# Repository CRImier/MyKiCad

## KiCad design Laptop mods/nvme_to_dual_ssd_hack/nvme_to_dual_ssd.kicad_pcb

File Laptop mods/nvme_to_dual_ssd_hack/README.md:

# M.2 NVMe to dual SSD adapter - with M.2 hack

This is an adapter board to put two SSDs in a M.2 slot that only accepts one,
it achieves that by abusing the PCI-E and M.2 specifications and relying on the
system firmware to be a bit deficient.

This adapter can only work in slots that accept either a PCI-E SSD or a SATA SSD.
It switches the slot into the SATA mode, but relies on PCI-E REFCLK and lanes 2&3
to be present. It uses lanes 2&3 as PCI-E lanes for the PCI-E SSD, connecting
lane 3 to SSD's lane 0 and lane 2 to SSD lane 1. This kind of lane reversal is
in the PCI-E spec, but it's not clear whether it's implemented in chipsets available out there,
and which chipsets it could be compatible with.

There's two ways to implement PCI-E/SATA muxing for an M.2 drive. First way relies on a
a Pericom-made (or similar) mux that switches either PCI-E or SATA to your M.2 slot,
depending on the CONFIG1 pin state. This means that both PCI-E and SATA are present
at the external mux, whereas REFCLK and PCI-E lanes 1-3 are hardwired to the slot.

Second way is where muxing is done inside the chipset itself, using hybrid lanes that
can be either PCI-E or SATA, depending on chipset's internal configuration. So, the CONFIG1
signal goes to the chipset, and the SSD is connected to the chipset directly, with all four lanes.
It's not clear if lanes 1-3 and REFCLK are disabled when a SATA SSD is inserted - if so,
this adapter will not work unless you somehow find a way for this not to happen.
Which is to say, if this adapter is used on a laptop with an internal mux, it relies on the
PCI-E lanes 1-3 and REFCLK to stay enabled.

At this point, I wish I had some kind of way to produce 100MHz REFCLK with an overall
small footprint. I really don't know... after all, REFCLK is often produced by a different
chip on the motherboard, or a different part of the chipset. Any ideas? Anyone?

You can only tell which kind of mux is being used by looking over the motherboard. If it has
a mux near the SSD socket, then it's an external mux kind of deal. If there's no mux
in sight, then the mux is inside the chipset. In fact, I have two Asus motherboards
that come from similar laptops, both equipped with a Ryzen 3500U (chipset on the same package
as CPU), yet one of them uses an external mux and one of them uses the internal one.
Of course, my daily driver laptop just had to be the one with the internal mux!

This adapter should be plug&play, *provided* that your hardware can be subverted in this kind of way.

This board has no decoupling capacitors, and you're on your own when it comes to managing 3.3V power draw
of two SSDs in a slot designed to power one. There seems to be enough 3.3V pins in an M-key slot for two SSDs,
conceptually (each M.2 pin is 0.5A max, 9x0.5A = 4.5A), but I give you no guarantees that it works out for you power-wise.

If your chipset disables the PCI-E when it detects a SATA SSD, I can't help you with that, I'm sorry.
Sometimes, if you have an external mux for that signal, the detection line also goes to the chipset -
then, you can track it down and break the connection.

There are resistors on the bottom for interrupting PCI-E&other control signals
if any of them interfere with operation of your SSD:

* 1 interrupts DAA/DSS
* 2 interrupts DEVSLP
* 3 interrupts PERST (PCI-E only)
* 4 interrupts CLKREQ (PCI-E only)
* 5 interrupts PEWAKE (PCI-E only)
* 6 interrupts SUSCLK

This board is untested and there's no guarantees of fitness.

- PCB size: 22x80mm
- Layer count: 2
- Recommended thickness: 0.8mm (it's an M.2 card, it has to be 0.8mm)

If you need this specific board, contact me - I don't sell it yet because it's untested. A less cursed (and actually tested) variation of this board is available on Tindie!

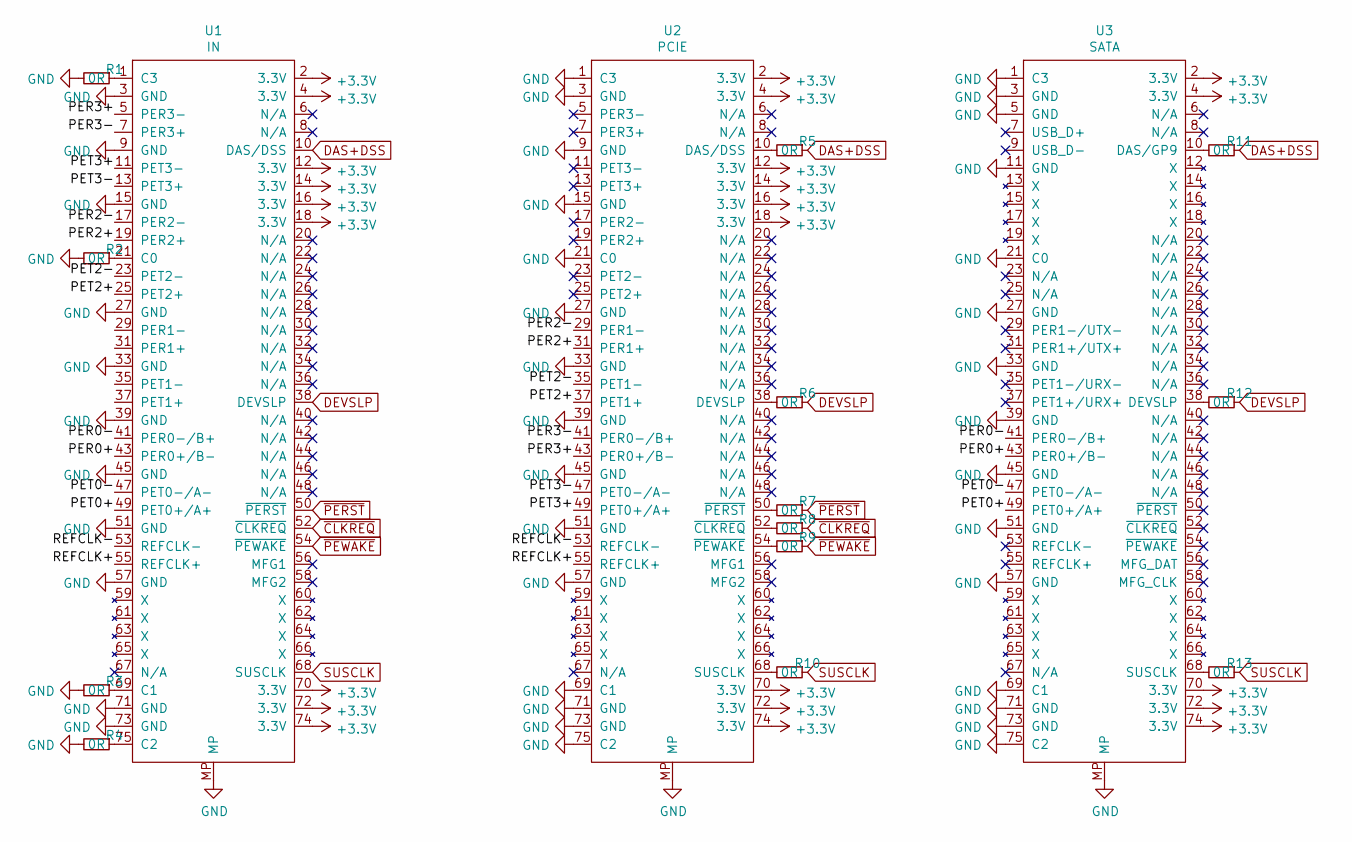
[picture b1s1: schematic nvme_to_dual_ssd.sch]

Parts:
R1, R2, R3, R4, R5, R6, R7, R8, R9, R10, R11, R12, R13: 0R; R_0402_1005Metric
U1: IN; NGFF_M
U2: PCIE; Conn_TE-M.2-0.5-67P-doublesided_TypeM
U3: SATA; Conn_TE-M.2-0.5-67P-doublesided_TypeB

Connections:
+3V3: U1.2 (3.3V), U1.4 (3.3V), U1.12 (3.3V), U1.14 (3.3V), U1.16 (3.3V), U1.18 (3.3V), U1.70 (3.3V), U1.72 (3.3V), U1.74 (3.3V), U2.2 (3.3V), U2.4 (3.3V), U2.12 (3.3V), U2.14 (3.3V), U2.16 (3.3V), U2.18 (3.3V), U2.70 (3.3V), U2.72 (3.3V), U2.74 (3.3V), U3.2 (3.3V), U3.4 (3.3V), U3.70 (3.3V), U3.72 (3.3V), U3.74 (3.3V)
/PER0+: U1.43 (PER0+/B-), U3.43 (PER0+/B-)
/PER0-: U1.41 (PER0-/B+), U3.41 (PER0-/B+)
/PER2+: U1.19 (PER2+), U2.31 (PER1+)
/PER2-: U1.17 (PER2-), U2.29 (PER1-)
/PER3+: U1.5 (PER3-), U2.43 (PER0+/B-)
/PER3-: U1.7 (PER3+), U2.41 (PER0-/B+)
/PET0+: U1.49 (PET0+/A+), U3.49 (PET0+/A+)
/PET0-: U1.47 (PET0-/A-), U3.47 (PET0-/A-)
/PET2+: U1.25 (PET2+), U2.37 (PET1+)
/PET2-: U1.23 (PET2-), U2.35 (PET1-)
/PET3+: U1.11 (PET3-), U2.49 (PET0+/A+)
/PET3-: U1.13 (PET3+), U2.47 (PET0-/A-)
/REFCLK+: U1.55 (REFCLK+), U2.55 (REFCLK+)
/REFCLK-: U1.53 (REFCLK-), U2.53 (REFCLK-)
DAS+DSS: R5.1, R11.1, U1.10 (DAS/DSS)
DEVSLP: R6.1, R12.1, U1.38 (DEVSLP)
GND: R1.2, R2.2, R3.2, R4.2, U1.3 (GND), U1.9 (GND), U1.15 (GND), U1.27 (GND), U1.33 (GND), U1.39 (GND), U1.45 (GND), U1.51 (GND), U1.57 (GND), U1.71 (GND), U1.73 (GND), U1.MP, U2.1 (C3), U2.3 (GND), U2.9 (GND), U2.15 (GND), U2.21 (C0), U2.27 (GND), U2.33 (GND), U2.39 (GND), U2.45 (GND), U2.51 (GND), U2.57 (GND), U2.69 (C1), U2.71 (GND), U2.73 (GND), U2.75 (C2), U2.MP, U3.1 (C3), U3.3 (GND), U3.5 (GND), U3.11 (GND), U3.21 (C0), U3.27 (GND), U3.33 (GND), U3.39 (GND), U3.45 (GND), U3.51 (GND), U3.57 (GND), U3.69 (C1), U3.71 (GND), U3.73 (GND), U3.75 (C2), U3.MP
unnamed: R1.1, U1.1 (C3)
unnamed: R2.1, U1.21 (C0)
unnamed: R3.1, U1.69 (C1)
unnamed: R4.1, U1.75 (C2)
unnamed: R5.2, U2.10 (DAS/DSS)
unnamed: R6.2, U2.38 (DEVSLP)
unnamed: R7.2, U2.50 (~PERST)
unnamed: R8.2, U2.52 (~CLKREQ)
unnamed: R9.2, U2.54 (~PEWAKE)
unnamed: R10.2, U2.68 (SUSCLK)
unnamed: R11.2, U3.10 (DAS/GP9)
unnamed: R12.2, U3.38 (DEVSLP)
unnamed: R13.2, U3.68 (SUSCLK)
SUSCLK: R10.1, R13.1, U1.68 (SUSCLK)
~CLKREQ: R8.1, U1.52 (~CLKREQ)
~PERST: R7.1, U1.50 (~PERST)
~PEWAKE: R9.1, U1.54 (~PEWAKE)

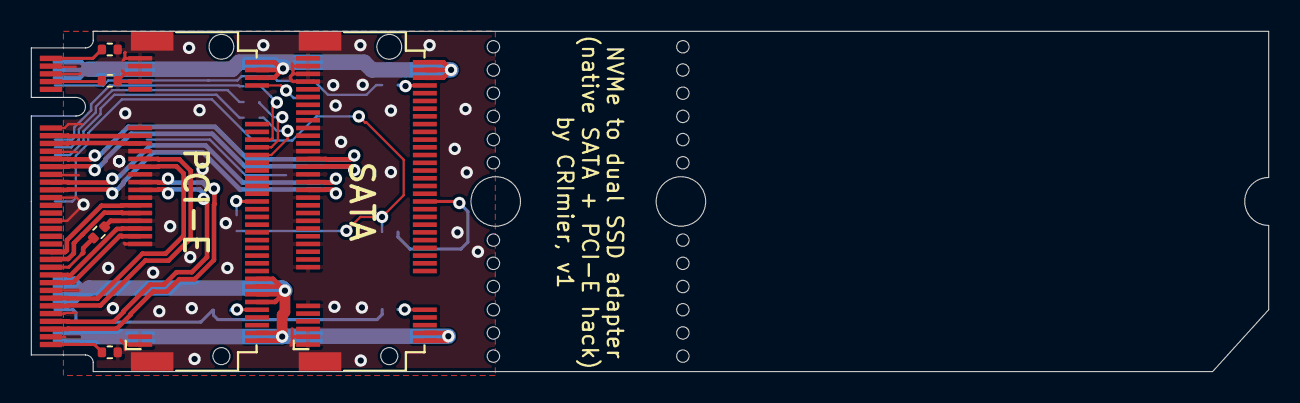
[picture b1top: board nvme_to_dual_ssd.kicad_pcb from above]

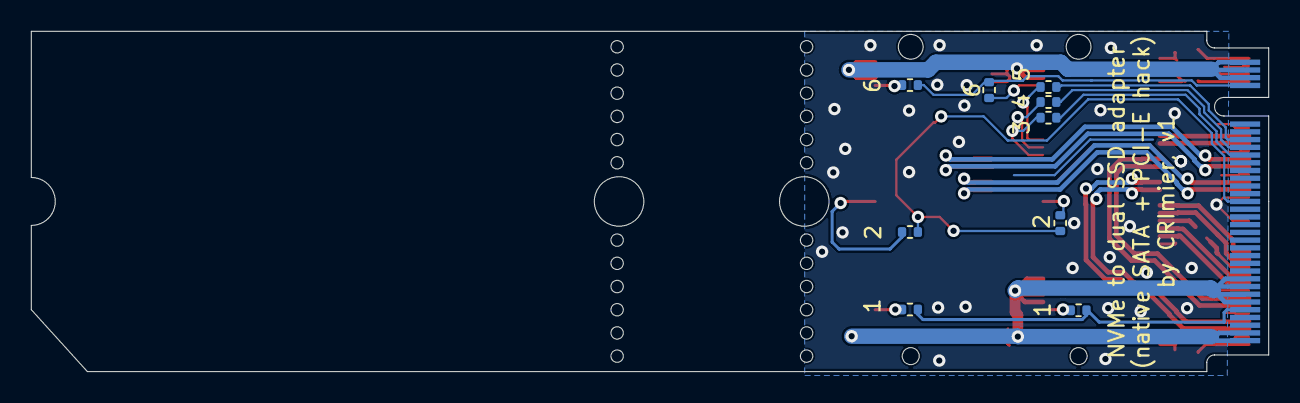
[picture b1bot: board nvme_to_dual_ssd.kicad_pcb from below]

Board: 2 copper layers, 80.0 x 22.0 mm, 16 parts (9 on the bottom side), 35 nets.

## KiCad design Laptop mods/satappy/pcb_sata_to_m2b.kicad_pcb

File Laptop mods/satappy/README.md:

# SATAppy

This is a board that plugs straight into a SATA socket - either one that supports a regular HDD, or one that supports
a laptop sized optical disk drive. It also has a M.2 SATA SSD socket (M-key, but hey).

This board allows you to wire up a SATA cable for any purpose. You can also tap, reconnect or the full-sized SATA power connector power rails.

The SATA routing is daring - this is a 2-layer board, with stubs. There's no redrivers of any kind, either. Impedance has been kinda decreased towards
the 100 ohm target, but not fully.

Currently, the board's outline is not great. I might fix it at some point. If you'd like to manufacture the design or work off it,
contact me, I can find one of these boards I got made and make adjustments to the outline. 

## Notes

- Signal names are silkscreened on the board, top and bottom layers.
- This board is untested and there's no guarantees of fitness.
- I recommend a stencil for assembling this board.

## Info

- Software: Kicad 7
- Version: 1
- PCB size: 25*46mm
- Layer count: 2
- Recommended thickness: 1.2mm (to fit into SATA sockets)

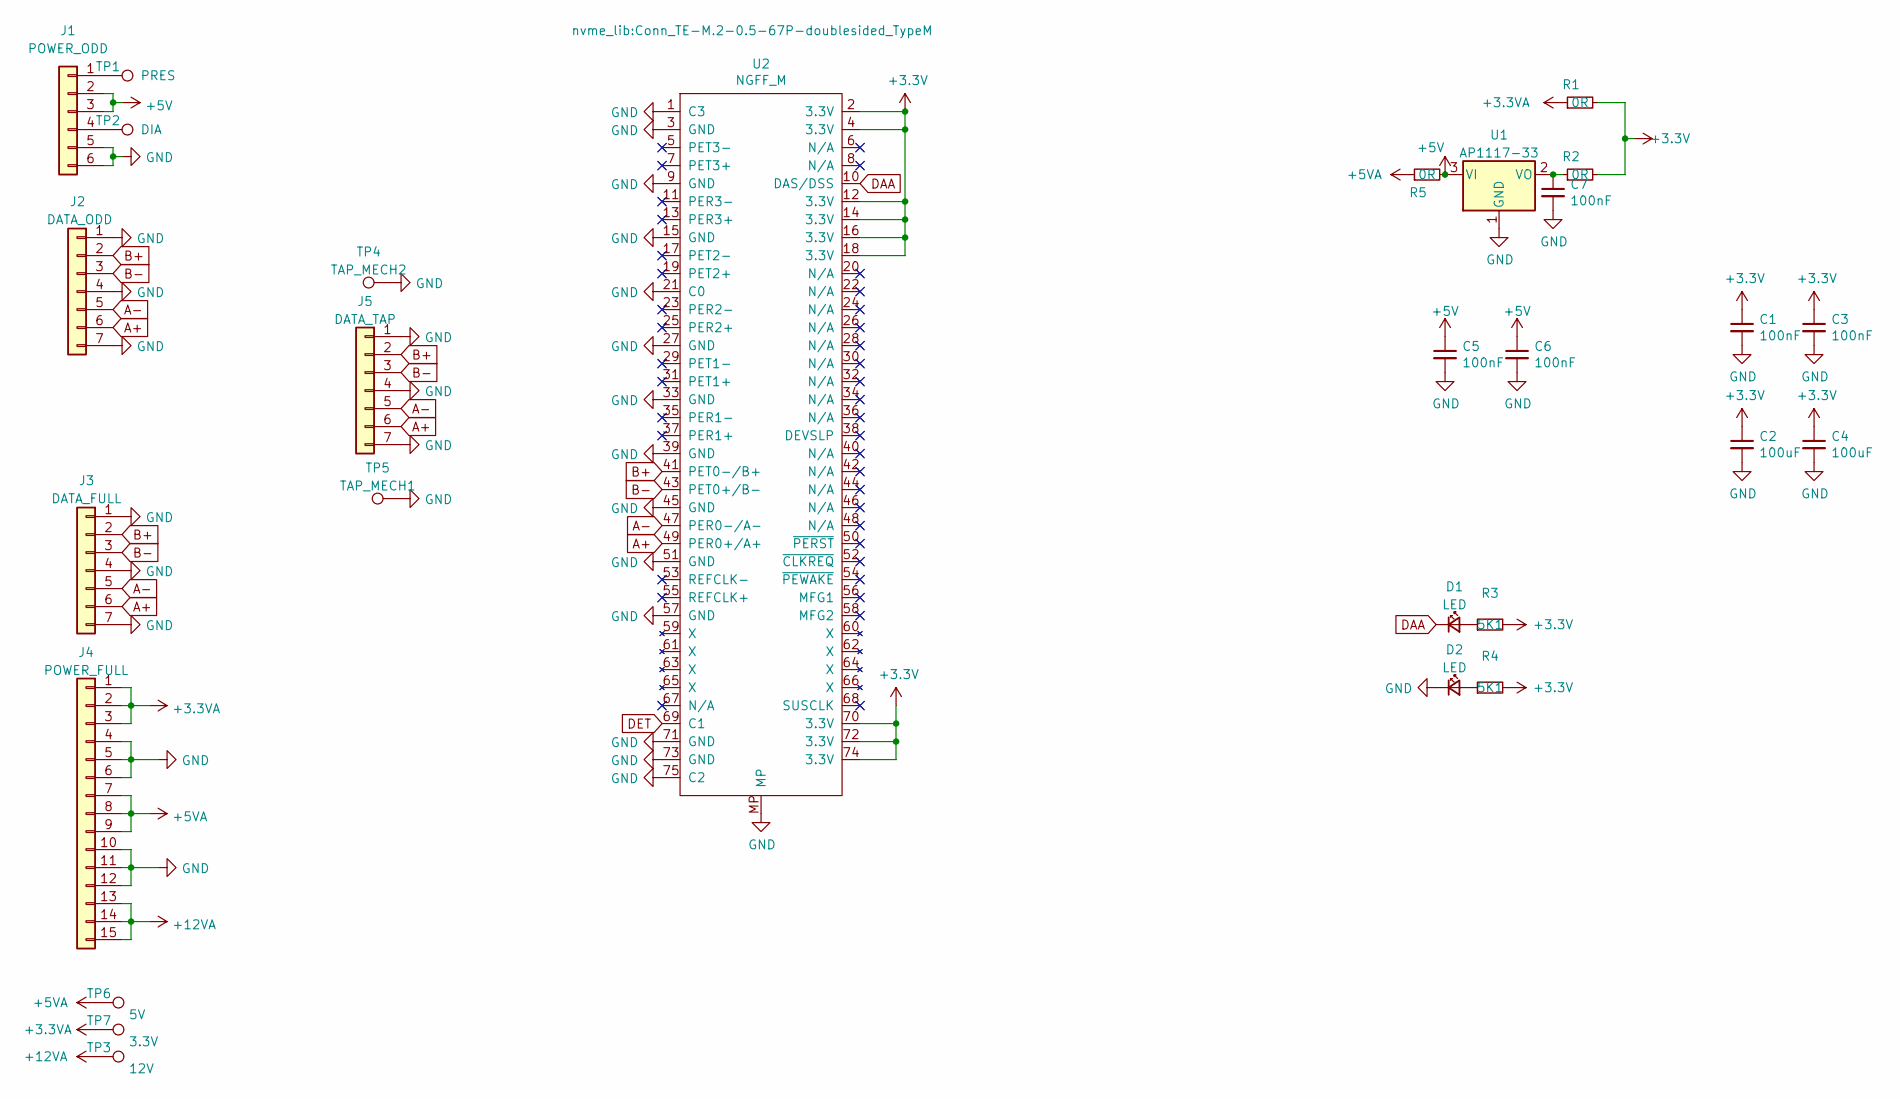
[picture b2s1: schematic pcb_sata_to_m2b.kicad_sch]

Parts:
C1, C3, C6: 100nF; C_0805_2012Metric
C2, C4: 100uF; CP_EIA-2012-12_Kemet-R_Pad1.30x1.05mm_HandSolder
C5, C7: 100nF; CP_EIA-3528-21_Kemet-B_Pad1.50x2.35mm_HandSolder
D1, D2: LED; D_0805_2012Metric
J1: POWER_ODD; SATA_POWER_ODD
J2: DATA_ODD; SATA_SMD
J3: DATA_FULL; SATA_SMD
J4: POWER_FULL; SATA_POWER_FULL
J5: DATA_TAP; PinSocket_1x07_P1.27mm_Vertical
R1, R2, R5: 0R; R_0805_2012Metric
R3, R4: 5K1; R_0603_1608Metric
TP1: PRES; TestPoint_THTPad_D1.5mm_Drill0.7mm
TP2: DIA; TestPoint_THTPad_D1.5mm_Drill0.7mm
TP3: 12V; TestPoint_THTPad_D1.5mm_Drill0.7mm
TP4: TAP_MECH2; TestPoint_Plated_Hole_D2.0mm
TP5: TAP_MECH1; TestPoint_Plated_Hole_D2.0mm
TP6: 5V; TestPoint_THTPad_D1.5mm_Drill0.7mm
TP7: 3.3V; TestPoint_THTPad_D1.5mm_Drill0.7mm
U1: AP1117-33; SOT-223-3_TabPin2
U2: NGFF_M; Conn_TE-M.2-0.5-67P-doublesided_TypeM

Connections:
+3.3VA: J4.1, J4.2, J4.3, R1.1, TP7.1
+3V3: C1.1, C2.1, C3.1, C4.1, R1.2, R2.2, R3.2, R4.2, U2.2 (3.3V), U2.4 (3.3V), U2.12 (3.3V), U2.14 (3.3V), U2.16 (3.3V), U2.18 (3.3V), U2.70 (3.3V), U2.72 (3.3V), U2.74 (3.3V)
+5V: C5.1, C6.1, J1.2, J1.3, R5.2, U1.3 (VI)
+5VA: J4.7, J4.8, J4.9, R5.1, TP6.1
+12VA: J4.13, J4.14, J4.15, TP3.1
A+: J2.6, J3.6, J5.6, U2.49 (PER0+/A+)
A-: J2.5, J3.5, J5.5, U2.47 (PER0-/A-)
B+: J2.2, J3.2, J5.2, U2.41 (PET0-/B+)
B-: J2.3, J3.3, J5.3, U2.43 (PET0+/B-)
DAA: D1.1 (K), U2.10 (DAS/DSS)
DET: U2.69 (C1)
GND: C1.2, C2.2, C3.2, C4.2, C5.2, C6.2, C7.2, D2.1 (K), J1.5, J1.6, J2.1, J2.4, J2.7, J3.1, J3.4, J3.7, J4.4, J4.5, J4.6, J4.10, J4.11, J4.12, J5.1, J5.4, J5.7, TP4.1, TP5.1, U1.1 (GND), U2.1 (C3), U2.3 (GND), U2.9 (GND), U2.15 (GND), U2.21 (C0), U2.27 (GND), U2.33 (GND), U2.39 (GND), U2.45 (GND), U2.51 (GND), U2.57 (GND), U2.71 (GND), U2.73 (GND), U2.75 (C2), U2.MP
unnamed: D1.2 (A), R3.1
unnamed: D2.2 (A), R4.1
unnamed: J1.1, TP1.1
unnamed: J1.4, TP2.1
unnamed: C7.1, R2.1, U1.2 (VO)

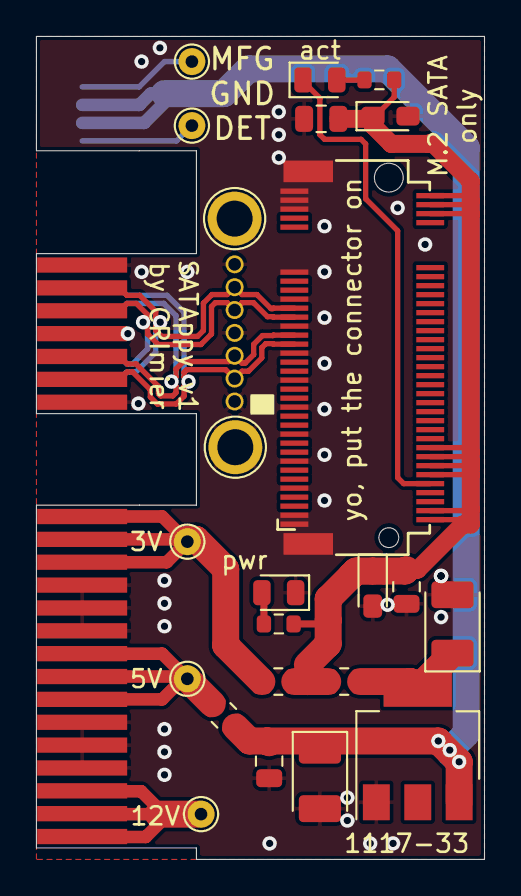
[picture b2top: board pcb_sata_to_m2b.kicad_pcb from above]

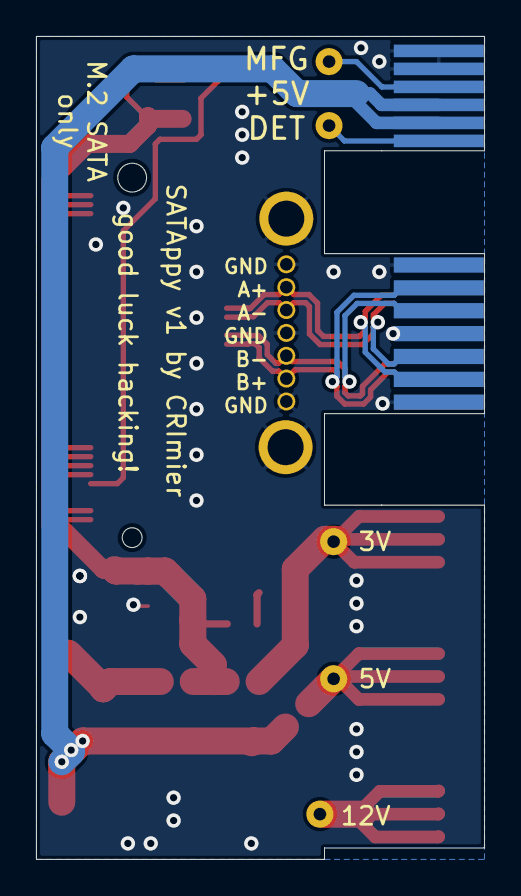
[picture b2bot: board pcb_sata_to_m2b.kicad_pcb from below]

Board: 2 copper layers, 24.9 x 45.7 mm, 28 parts (2 on the bottom side), 16 nets.

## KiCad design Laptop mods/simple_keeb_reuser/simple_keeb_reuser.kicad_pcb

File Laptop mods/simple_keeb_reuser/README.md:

# Simple Keeb Reuser 

This is basically an SPI GPIO expander with 32 bits, designed at laptop keyboard reuse.
PCF8574-like, it has low-strength default pullups and strong pulldowns you can enable.
It's chip shortage-proof, sorta - it's a combination of 595 and 165 chips.
It has two SPI ports, one input-only and one output-only - they're joined into a single port by default.

It's designed for reusing laptop keyboards on the cheap. 
I've designed this during chip shortage times, and never made use of it.
I recommend you use ready-to-go I2C or SPI expander ICs like a normal person.
This is more of a decent test for pick&place machines, at this point.

Has connectors for 1mm, 0.5mm and 0.8mm pitch FPCs, up to 32 pins.

## Notes

- Signal names are silkscreened on the board's bottom layer.
- This repository also includes files for manufacturing a 2x2 panel.
- This board is untested and there's no guarantees of fitness.
- I recommend a stencil for assembling this board - purely for saving yourself some grief, and because of the FPCs, too.

## Info

- Software: Kicad 6
- Version: 1
- PCB size: 49*44mm
- Layer count: 2

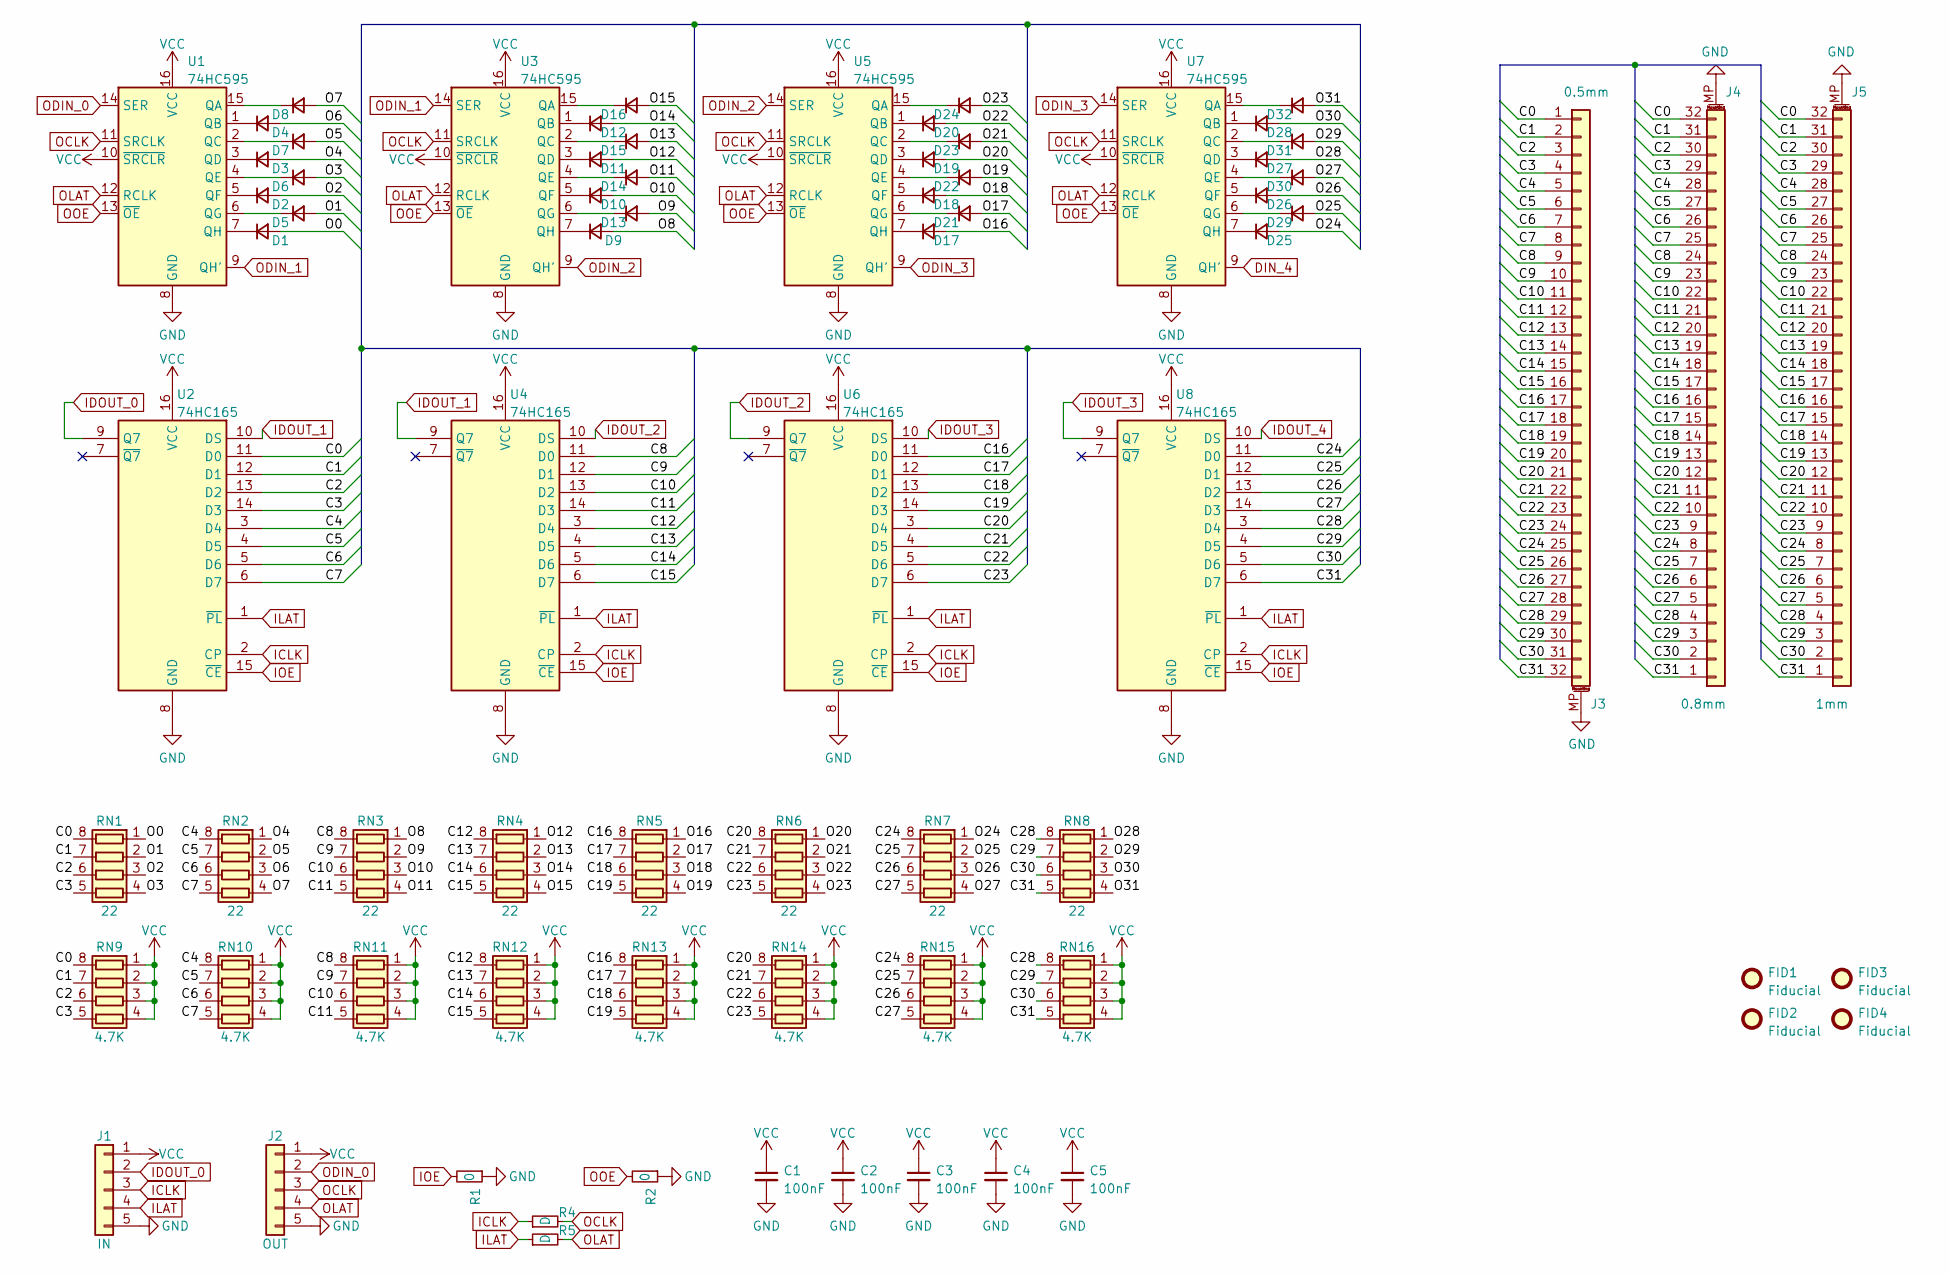
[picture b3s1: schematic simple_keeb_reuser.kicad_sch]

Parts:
C1, C2, C3, C4, C5: 100nF; C_0805_2012Metric
D1, D2, D3, D4, D5, D6, D7, D8, D9, D10, D11, D12, D13, D14, D15, D16, D17, D18, D19, D20, D21, D22, D23, D24, D25, D26, D27, D28, D29, D30, D31, D32: D; D_SOD-123F
FID1, FID2, FID3, FID4: Fiducial; Fiducial_0.75mm_Mask1.5mm
J1: IN; PinHeader_1x05_P2.54mm_Vertical
J2: OUT; PinHeader_1x05_P2.54mm_Vertical
J3: 0.5mm; FPC_40_0.5mm
J4: 0.8mm; FPC_40_0.8mm
J5: 1mm; FPC_40_1mm
R1, R2: 0; R_0603_1608Metric
R4, R5: D; R_0603_1608Metric
RN1, RN2, RN3, RN4, RN5, RN6, RN7, RN8: 22; R_Array_Convex_4x0603
RN9, RN10, RN11, RN12, RN13, RN14, RN15, RN16: 4.7K; R_Array_Convex_4x0603
U1, U3, U5, U7: 74HC595; SO-16_3.9x9.9mm_P1.27mm
U2, U4, U6, U8: 74HC165; SO-16_3.9x9.9mm_P1.27mm

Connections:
/C0: J3.1, J4.32, J5.32, RN1.8 (R1.2), RN9.8 (R1.2), U2.11 (D0)
/C1: J3.2, J4.31, J5.31, RN1.7 (R2.2), RN9.7 (R2.2), U2.12 (D1)
/C2: J3.3, J4.30, J5.30, RN1.6 (R3.2), RN9.6 (R3.2), U2.13 (D2)
/C3: J3.4, J4.29, J5.29, RN1.5 (R4.2), RN9.5 (R4.2), U2.14 (D3)
/C4: J3.5, J4.28, J5.28, RN2.8 (R1.2), RN10.8 (R1.2), U2.3 (D4)
/C5: J3.6, J4.27, J5.27, RN2.7 (R2.2), RN10.7 (R2.2), U2.4 (D5)
/C6: J3.7, J4.26, J5.26, RN2.6 (R3.2), RN10.6 (R3.2), U2.5 (D6)
/C7: J3.8, J4.25, J5.25, RN2.5 (R4.2), RN10.5 (R4.2), U2.6 (D7)
/C8: J3.9, J4.24, J5.24, RN3.8 (R1.2), RN11.8 (R1.2), U4.11 (D0)
/C9: J3.10, J4.23, J5.23, RN3.7 (R2.2), RN11.7 (R2.2), U4.12 (D1)
/C10: J3.11, J4.22, J5.22, RN3.6 (R3.2), RN11.6 (R3.2), U4.13 (D2)
/C11: J3.12, J4.21, J5.21, RN3.5 (R4.2), RN11.5 (R4.2), U4.14 (D3)
/C12: J3.13, J4.20, J5.20, RN4.8 (R1.2), RN12.8 (R1.2), U4.3 (D4)
/C13: J3.14, J4.19, J5.19, RN4.7 (R2.2), RN12.7 (R2.2), U4.4 (D5)
/C14: J3.15, J4.18, J5.18, RN4.6 (R3.2), RN12.6 (R3.2), U4.5 (D6)
/C15: J3.16, J4.17, J5.17, RN4.5 (R4.2), RN12.5 (R4.2), U4.6 (D7)
/C16: J3.17, J4.16, J5.16, RN5.8 (R1.2), RN13.8 (R1.2), U6.11 (D0)
/C17: J3.18, J4.15, J5.15, RN5.7 (R2.2), RN13.7 (R2.2), U6.12 (D1)
/C18: J3.19, J4.14, J5.14, RN5.6 (R3.2), RN13.6 (R3.2), U6.13 (D2)
/C19: J3.20, J4.13, J5.13, RN5.5 (R4.2), RN13.5 (R4.2), U6.14 (D3)
/C20: J3.21, J4.12, J5.12, RN6.8 (R1.2), RN14.8 (R1.2), U6.3 (D4)
/C21: J3.22, J4.11, J5.11, RN6.7 (R2.2), RN14.7 (R2.2), U6.4 (D5)
/C22: J3.23, J4.10, J5.10, RN6.6 (R3.2), RN14.6 (R3.2), U6.5 (D6)
/C23: J3.24, J4.9, J5.9, RN6.5 (R4.2), RN14.5 (R4.2), U6.6 (D7)
/C24: J3.25, J4.8, J5.8, RN7.8 (R1.2), RN15.8 (R1.2), U8.11 (D0)
/C25: J3.26, J4.7, J5.7, RN7.7 (R2.2), RN15.7 (R2.2), U8.12 (D1)
/C26: J3.27, J4.6, J5.6, RN7.6 (R3.2), RN15.6 (R3.2), U8.13 (D2)
/C27: J3.28, J4.5, J5.5, RN7.5 (R4.2), RN15.5 (R4.2), U8.14 (D3)
/C28: J3.29, J4.4, J5.4, RN8.8 (R1.2), RN16.8 (R1.2), U8.3 (D4)
/C29: J3.30, J4.3, J5.3, RN8.7 (R2.2), RN16.7 (R2.2), U8.4 (D5)
/C30: J3.31, J4.2, J5.2, RN8.6 (R3.2), RN16.6 (R3.2), U8.5 (D6)
/C31: J3.32, J4.1, J5.1, RN8.5 (R4.2), RN16.5 (R4.2), U8.6 (D7)
/O0: D1.2 (A), RN1.1 (R1.1)
/O1: D5.2 (A), RN1.2 (R2.1)
/O2: D2.2 (A), RN1.3 (R3.1)
/O3: D6.2 (A), RN1.4 (R4.1)
/O4: D3.2 (A), RN2.1 (R1.1)
/O5: D7.2 (A), RN2.2 (R2.1)
/O6: D4.2 (A), RN2.3 (R3.1)
/O7: D8.2 (A), RN2.4 (R4.1)
/O8: D9.2 (A), RN3.1 (R1.1)
/O9: D13.2 (A), RN3.2 (R2.1)
/O10: D10.2 (A), RN3.3 (R3.1)
/O11: D14.2 (A), RN3.4 (R4.1)
/O12: D11.2 (A), RN4.1 (R1.1)
/O13: D15.2 (A), RN4.2 (R2.1)
/O14: D12.2 (A), RN4.3 (R3.1)
/O15: D16.2 (A), RN4.4 (R4.1)
/O16: D17.2 (A), RN5.1 (R1.1)
/O17: D21.2 (A), RN5.2 (R2.1)
/O18: D18.2 (A), RN5.3 (R3.1)
/O19: D22.2 (A), RN5.4 (R4.1)
/O20: D19.2 (A), RN6.1 (R1.1)
/O21: D23.2 (A), RN6.2 (R2.1)
/O22: D20.2 (A), RN6.3 (R3.1)
/O23: D24.2 (A), RN6.4 (R4.1)
/O24: D25.2 (A), RN7.1 (R1.1)
/O25: D29.2 (A), RN7.2 (R2.1)
/O26: D26.2 (A), RN7.3 (R3.1)
/O27: D30.2 (A), RN7.4 (R4.1)
/O28: D27.2 (A), RN8.1 (R1.1)
/O29: D31.2 (A), RN8.2 (R2.1)
/O30: D28.2 (A), RN8.3 (R3.1)
/O31: D32.2 (A), RN8.4 (R4.1)
DIN_4: U7.9 (QH')
GND: C1.2, C2.2, C3.2, C4.2, C5.2, J1.5, J2.5, J3.MP (MountPin), J4.MP (MountPin), J5.MP (MountPin), R1.1, R2.1, U1.8 (GND), U2.8 (GND), U3.8 (GND), U4.8 (GND), U5.8 (GND), U6.8 (GND), U7.8 (GND), U8.8 (GND)
ICLK: J1.3, R4.1, U2.2 (CP), U4.2 (CP), U6.2 (CP), U8.2 (CP)
IDOUT_0: J1.2, U2.9 (Q7)
IDOUT_1: U2.10 (DS), U4.9 (Q7)
IDOUT_2: U4.10 (DS), U6.9 (Q7)
IDOUT_3: U6.10 (DS), U8.9 (Q7)
IDOUT_4: U8.10 (DS)
ILAT: J1.4, R5.1, U2.1 (~PL), U4.1 (~PL), U6.1 (~PL), U8.1 (~PL)
IOE: R1.2, U2.15 (~CE), U4.15 (~CE), U6.15 (~CE), U8.15 (~CE)
unnamed: D6.1 (K), U1.4 (QE)
unnamed: D7.1 (K), U1.2 (QC)
unnamed: D8.1 (K), U1.15 (QA)
unnamed: D9.1 (K), U3.7 (QH)
unnamed: D10.1 (K), U3.5 (QF)
unnamed: D11.1 (K), U3.3 (QD)
unnamed: D12.1 (K), U3.1 (QB)
unnamed: D13.1 (K), U3.6 (QG)
unnamed: D14.1 (K), U3.4 (QE)
unnamed: D15.1 (K), U3.2 (QC)
unnamed: D16.1 (K), U3.15 (QA)
unnamed: D26.1 (K), U7.5 (QF)
unnamed: D27.1 (K), U7.3 (QD)
unnamed: D28.1 (K), U7.1 (QB)
unnamed: D29.1 (K), U7.6 (QG)
unnamed: D30.1 (K), U7.4 (QE)
unnamed: D31.1 (K), U7.2 (QC)
unnamed: D32.1 (K), U7.15 (QA)
unnamed: D4.1 (K), U1.1 (QB)
unnamed: D3.1 (K), U1.3 (QD)
unnamed: D2.1 (K), U1.5 (QF)
unnamed: D5.1 (K), U1.6 (QG)
unnamed: D1.1 (K), U1.7 (QH)
unnamed: D20.1 (K), U5.1 (QB)
unnamed: D23.1 (K), U5.2 (QC)
unnamed: D19.1 (K), U5.3 (QD)
unnamed: D22.1 (K), U5.4 (QE)
unnamed: D18.1 (K), U5.5 (QF)
unnamed: D21.1 (K), U5.6 (QG)
unnamed: D17.1 (K), U5.7 (QH)
unnamed: D24.1 (K), U5.15 (QA)
unnamed: D25.1 (K), U7.7 (QH)
OCLK: J2.3, R4.2, U1.11 (SRCLK), U3.11 (SRCLK), U5.11 (SRCLK), U7.11 (SRCLK)
ODIN_0: J2.2, U1.14 (SER)
ODIN_1: U1.9 (QH'), U3.14 (SER)
ODIN_2: U3.9 (QH'), U5.14 (SER)
ODIN_3: U5.9 (QH'), U7.14 (SER)
OLAT: J2.4, R5.2, U1.12 (RCLK), U3.12 (RCLK), U5.12 (RCLK), U7.12 (RCLK)
OOE: R2.2, U1.13 (~OE), U3.13 (~OE), U5.13 (~OE), U7.13 (~OE)
VCC: C1.1, C2.1, C3.1, C4.1, C5.1, J1.1, J2.1, RN9.1 (R1.1), RN9.2 (R2.1), RN9.3 (R3.1), RN9.4 (R4.1), RN10.1 (R1.1), RN10.2 (R2.1), RN10.3 (R3.1), RN10.4 (R4.1), RN11.1 (R1.1), RN11.2 (R2.1), RN11.3 (R3.1), RN11.4 (R4.1), RN12.1 (R1.1), RN12.2 (R2.1), RN12.3 (R3.1), RN12.4 (R4.1), RN13.1 (R1.1), RN13.2 (R2.1), RN13.3 (R3.1), RN13.4 (R4.1), RN14.1 (R1.1), RN14.2 (R2.1), RN14.3 (R3.1), RN14.4 (R4.1), RN15.1 (R1.1), RN15.2 (R2.1), RN15.3 (R3.1), RN15.4 (R4.1), RN16.1 (R1.1), RN16.2 (R2.1), RN16.3 (R3.1), RN16.4 (R4.1), U1.10 (~SRCLR), U1.16 (VCC), U2.16 (VCC), U3.10 (~SRCLR), U3.16 (VCC), U4.16 (VCC), U5.10 (~SRCLR), U5.16 (VCC), U6.16 (VCC), U7.10 (~SRCLR), U7.16 (VCC), U8.16 (VCC)

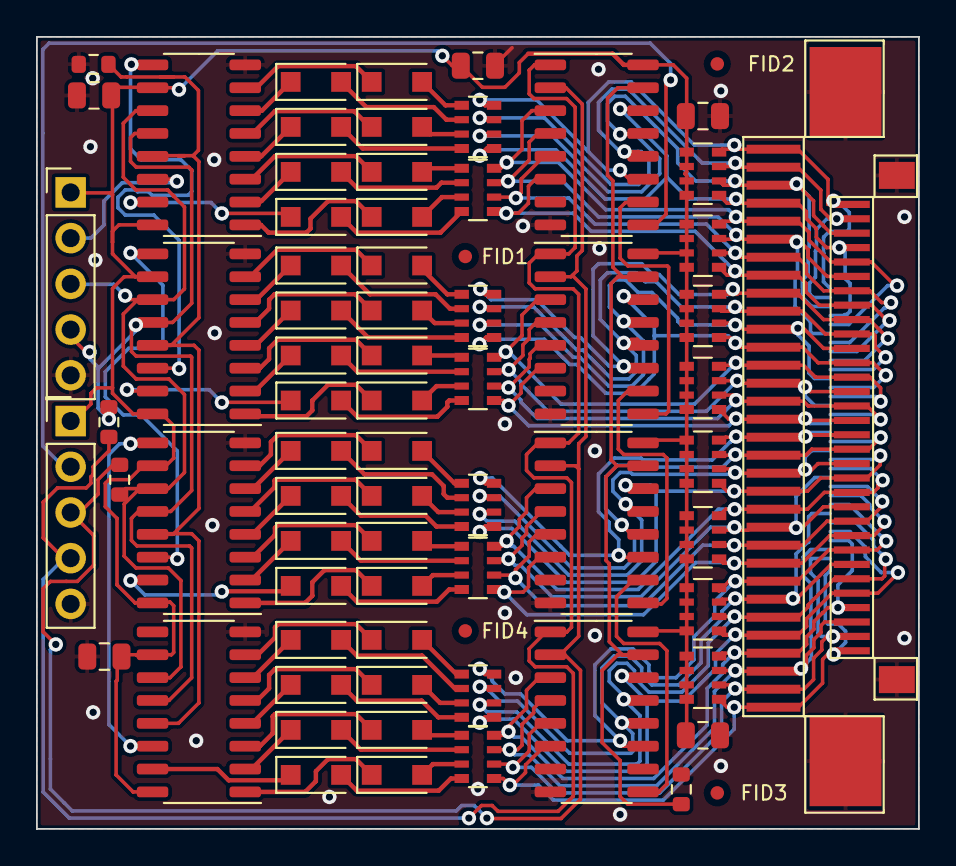
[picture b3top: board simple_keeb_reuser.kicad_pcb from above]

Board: 2 copper layers, 49.0 x 44.0 mm, 74 parts (1 on the bottom side), 112 nets.

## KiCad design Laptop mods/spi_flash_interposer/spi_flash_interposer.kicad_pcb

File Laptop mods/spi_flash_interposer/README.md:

# SPI flash switcher

Do you want to run custom BIOS images? Quickly test your BIOS changes without constant reflashing?
Easily and safely reprogram the BIOS chip at any moment in an external programmer? Switch between two BIOS versions on the fly?

This interposer board that should help you with that. It has footprints for two SOIC8-W flash chips
and a switch that selects one of these chips to be active. It accomplishes that with tri-state buffers
that switch CS and DO SPI signals, disconnecting either of the flash chips from the board and connecting the other one.

The board has buffers that are rated for both 3.3V and 1.8V operation, making this board suitable
for modern 1.8V SPI motherboards. In addition to that, if you need more granularity in which signals
go to which chip (i.e. you want to make one chip's write protect pin disabled to prevent accidental overwrites), 
there are 0R resistors you can remove to isolate any line from any chip.

You connect this interposer by desoldering the original BIOS IC from the motherboard and soldering the IC onto the interposer, 
then using a 8-pin ribbon cable to connect the interposer to the motherboard. The board pinout is selected
in a way that you can layout a ribbon cable from the interposer to the motherboard without crossing any wires, as pictured
in the schematic.

Signal names are silkscreened on the board's bottom layer.

- PCB size: 36.5x15.5mm
- Layer count: 2
- Recommended thickness: thin (so that it fits inside the laptop well)

This board is available on Tindie!

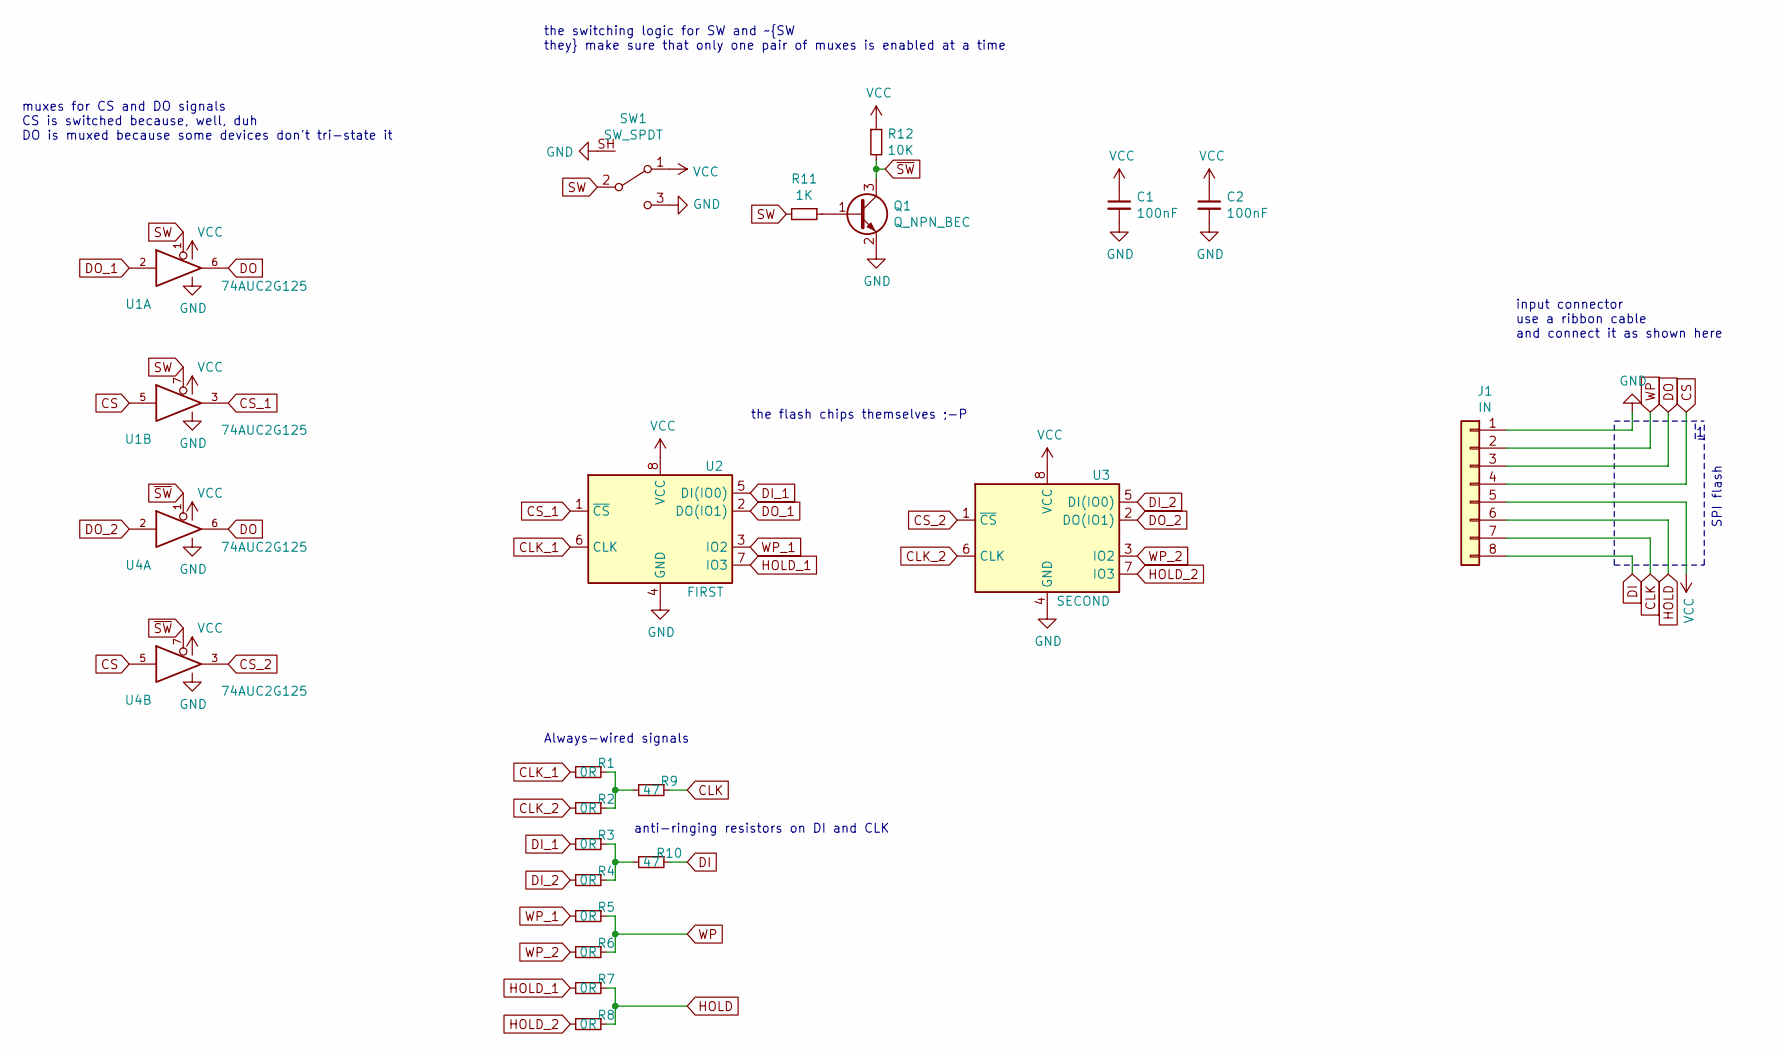
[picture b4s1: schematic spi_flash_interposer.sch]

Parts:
C1, C2: 100nF; C_0603_1608Metric
J1: IN; PinHeader_1x08_P2.00mm_Vertical
Q1: Q_NPN_BEC; SOT-23
R1, R2, R3, R4, R5, R6, R7, R8: 0R; R_0402_1005Metric_Pad0.72x0.64mm_HandSolder
R9, R10: 47; R_0603_1608Metric
R11: 1K; R_0603_1608Metric
R12: 10K; R_0603_1608Metric
SW1: SW_SPDT; SW_SPDT_PCM12
U1, U4: 74AUC2G125; VSSOP-8_2.3x2mm_P0.5mm
U2: FIRST; SOIC-8_5.23x5.23mm_P1.27mm
U3: SECOND; SOIC-8_5.23x5.23mm_P1.27mm

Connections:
CLK: J1.7, R9.1
CLK_1: R1.2, U2.6 (CLK)
CLK_2: R2.2, U3.6 (CLK)
CS: J1.4, U1.5, U4.5
CS_1: U1.3, U2.1 (~CS)
CS_2: U3.1 (~CS), U4.3
DI: J1.8, R10.1
DI_1: R3.2, U2.5 (DI(IO0))
DI_2: R4.2, U3.5 (DI(IO0))
DO: J1.3, U1.6, U4.6
DO_1: U1.2, U2.2 (DO(IO1))
DO_2: U3.2 (DO(IO1)), U4.2
GND: C1.2, C2.2, J1.1, Q1.2 (E), SW1.3 (C), SW1.SH, U1.4 (GND), U2.4 (GND), U3.4 (GND), U4.4 (GND)
HOLD: J1.6, R7.1, R8.1
HOLD_1: R7.2, U2.7 (IO3)
HOLD_2: R8.2, U3.7 (IO3)
unnamed: Q1.1 (B), R11.1
unnamed: R1.1, R2.1, R9.2
unnamed: R3.1, R4.1, R10.2
SW: R11.2, SW1.2 (B), U1.1, U1.7
VCC: C1.1, C2.1, J1.5, R12.1, SW1.1 (A), U1.8 (VCC), U2.8 (VCC), U3.8 (VCC), U4.8 (VCC)
WP: J1.2, R5.1, R6.1
WP_1: R5.2, U2.3 (IO2)
WP_2: R6.2, U3.3 (IO2)
~SW: Q1.3 (C), R12.2, U4.1, U4.7

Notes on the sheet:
Always-wired signals
the switching logic for SW and ~SW they make sure that only one pair of muxes is enabled at a time
muxes for CS and DO signals CS is switched because, well, duh DO is muxed because some devices don't tri-state it
anti-ringing resistors on DI and CLK
the flash chips themselves ;-P
input connector use a ribbon cable and connect it as shown here
SPI flash

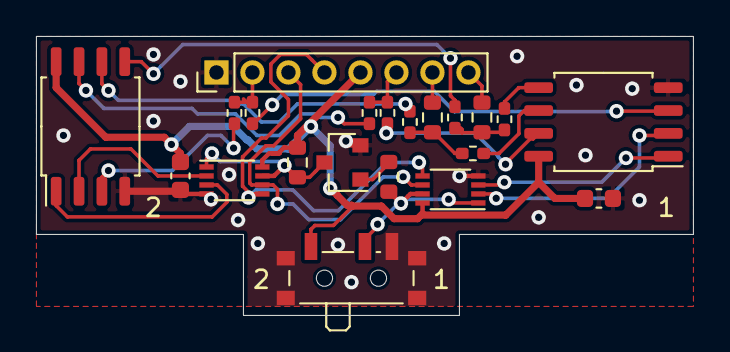
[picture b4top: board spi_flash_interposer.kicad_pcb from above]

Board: 2 copper layers, 36.5 x 15.5 mm, 21 parts (0 on the bottom side), 25 nets.

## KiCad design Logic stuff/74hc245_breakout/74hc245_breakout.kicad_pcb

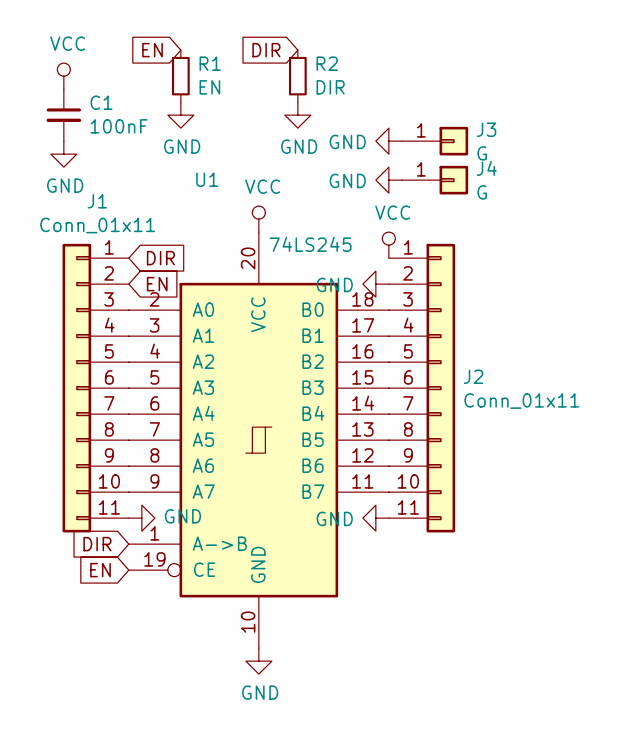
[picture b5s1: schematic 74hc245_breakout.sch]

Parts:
C1: 100nF; C_0805_2012Metric_Pad1.15x1.40mm_HandSolder
J1, J2: Conn_01x11; PinHeader_1x11_P2.54mm_Vertical
J3, J4: G; PinHeader_1x01_P2.54mm_Vertical
R1: EN; R_0805_2012Metric_Pad1.15x1.40mm_HandSolder
R2: DIR; R_0805_2012Metric_Pad1.15x1.40mm_HandSolder
U1: 74LS245; DIP-20_W7.62mm

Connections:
DIR: J1.1, R2.1, U1.1 (A->B)
EN: J1.2, R1.1, U1.19 (CE)
GND: C1.2, J1.11, J2.2, J2.11, J3.1, J4.1, R1.2, R2.2, U1.10 (GND)
unnamed: J1.3, U1.2 (A0)
unnamed: J1.4, U1.3 (A1)
unnamed: J1.5, U1.4 (A2)
unnamed: J1.6, U1.5 (A3)
unnamed: J1.7, U1.6 (A4)
unnamed: J1.8, U1.7 (A5)
unnamed: J1.9, U1.8 (A6)
unnamed: J1.10, U1.9 (A7)
unnamed: J2.3, U1.18 (B0)
unnamed: J2.4, U1.17 (B1)
unnamed: J2.5, U1.16 (B2)
unnamed: J2.6, U1.15 (B3)
unnamed: J2.7, U1.14 (B4)
unnamed: J2.8, U1.13 (B5)
unnamed: J2.9, U1.12 (B6)
unnamed: J2.10, U1.11 (B7)
VCC: C1.1, J2.1, U1.20 (VCC)

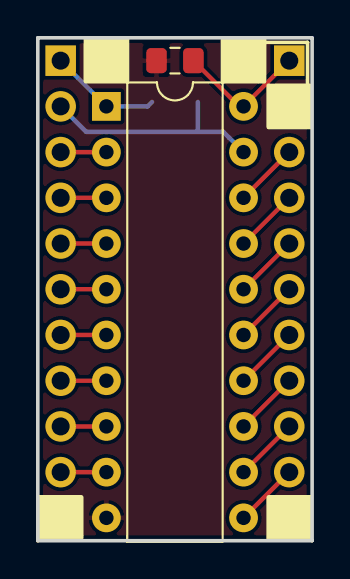
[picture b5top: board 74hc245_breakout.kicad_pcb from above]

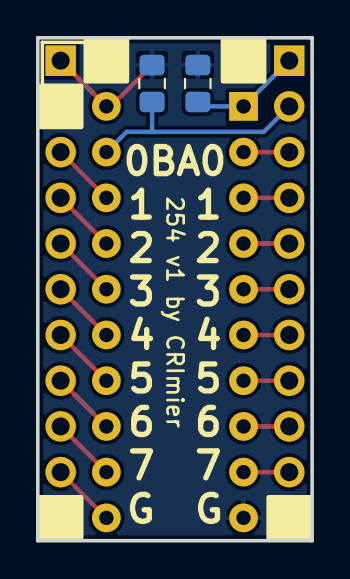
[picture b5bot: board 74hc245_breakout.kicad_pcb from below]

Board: 2 copper layers, 15.2 x 27.9 mm, 8 parts (2 on the bottom side), 20 nets.
